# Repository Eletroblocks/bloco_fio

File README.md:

# fio
Transmite a energia elétrica recebida para um bloco distante.

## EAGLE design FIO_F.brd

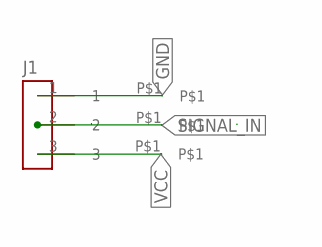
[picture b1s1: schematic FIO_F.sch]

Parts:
J1: CONECTOR_FEMEA; 3CONECTOR
U$1, U$2: PAD
VCC: PAD

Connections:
GND: J1.1, U$1.P$1
SIGNAL_IN: J1.2, U$2.P$1
VCC: J1.3, VCC.P$1

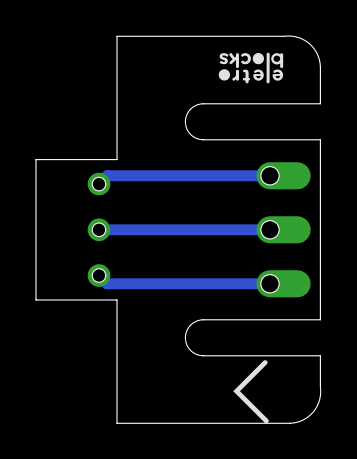
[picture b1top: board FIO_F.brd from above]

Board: 2 copper layers, 15.8 x 21.5 mm, 4 parts (0 on the bottom side), 3 nets.

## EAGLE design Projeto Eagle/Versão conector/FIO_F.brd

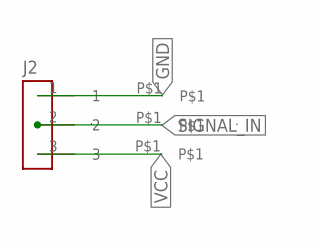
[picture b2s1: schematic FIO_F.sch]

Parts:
J2: CONECTOR_FEMEA; 3CONECTOR
J4: PAD
U$1: PAD
VCC: PAD

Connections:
GND: J2.1, U$1.P$1
SIGNAL_IN: J2.2, J4.P$1
VCC: J2.3, VCC.P$1

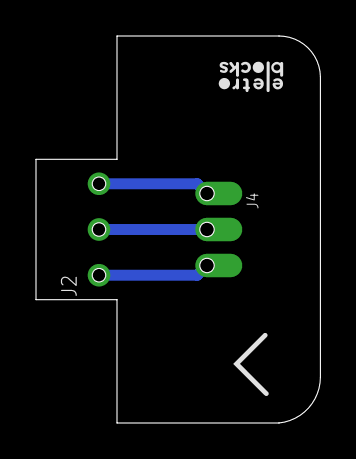
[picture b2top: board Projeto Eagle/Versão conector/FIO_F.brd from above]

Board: 2 copper layers, 15.8 x 21.5 mm, 4 parts (0 on the bottom side), 3 nets.

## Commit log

2020-11-23 init project
2020-11-23 correção de pads e adição de label de versionamento
2020-12-28 organizando arquivos
2020-12-28 imagem
